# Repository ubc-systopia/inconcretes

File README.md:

<!-- # IVP System Guide -->

This repository contains source code and build documentation for a physical inverted pendulum test platform. The physical system, seen below, works to keep the pendulum shaft upright by actuating a pendulum cart along a track. To achieve this, we use a PID controller program that runs on a network of 4 Raspberry Pis. The Pis are able to communicate with each other using a distributed key value store. 

## Controls

### PID Control

PID Control is used to actuate system and balance the pendulum. There are 2 PID algorithms running at different sampling rates (30 Hz for Position PID and 200 Hz for Angle PID were lower bounds in our testing). 

The PID algorithm tracks the error of a system over time and applies the following computation to it:

$$
  u(t)=K_pe(t)+ K_i \int_{a}^{b} e(\tau) \,d\tau + K_d \frac{d}{dt} e(t)
$$
<!--  -->
<!--  -->

The proportional term of $K_pe(t)$ can be thought of as **reacting immediately to the current error**, the integralterm as **accumulating past errors over time**, and the derivative as **predicting future error trends**. PID control offers a cost-effective and straightforward solution compared to more complex control methods. 

The position PID algorithm takes the Cart Position as an input. This is given by an ultrasonic sensors on the sides of the assembly, then filtered before being passed as an input. The position PID algorithm then computes an output which we call an Angle Offset. This is an offset to the real angle of the pendulum and works to amplify the response of the angle controller when the cart nears the edges of the track. Without this controller, the pendulum has no incentive to remain with the bounds of the track.

The angle controller takes the current angle of the pendulum along with the offset provided by the position controller and computes the appropriate signal to send to the motor accordingly. A larger deviation from the desired angle results in more force applied by the motor to correct the pendulum.

## System Overview

### Starting with a Single Node Setup

A diagram for the system for a single node configuration is seen above.  

The physical build consists of the pendulum itself, with a Rotary Encoder, 2 Ultrasonic sensors, 2 limit switches and a motor driver. 

In order to control the pendulum we periodically drive the motor on the pendulum using a PWM signal, which is scaled and given direction based on the state of the system, using the PID scheme outlined above.

The single node in the setup is running 2 periodic tasks at different periods, a **Position Control Loop** and an **Angle Control Loop**. At the Position Control Loop we read a filtered position of the cart and use this as input to the Position PID algorithm. The output is saved to our Key Value Store and is shared with the Angle Control Loop through a shared memory location. 

The **Rotary Encoder BP** is a microcontroller running a continuous loop which reads the **Rotary Encoder** to find the current angle of the pendulum in every loop and forwards this value to the **Angle Control Loop**. The **Angle Control Loop** also receives a reading for the cart's current position along the track from **Ultrasonic 1**. 

 The **Angle Control Loop** performs some filtering of the position and shared this back to the Position Control Loop through a shared memory location. The **Angle Control Loop** uses the output of the position control loop for the angle PID algorithm to give us the output to the Pendulum. This output is in the form a scalar value that is then translated to the duty cycle and direction of a PWM signal.

The **Motor BP** is another microcontroller that is running a continuous loop where it receives the PWM signal from the **Angle Control Loop** and forwards it to the motor driver which then actuates the actual pendulum to achieve control. 

### Moving to a Multi Node Setup

<!--  -->

In a Multi Node Setup,, we have a maximum of 4 Raspberry Pi Nodes. Each of these is running an **Angle Control Loop** and a **Position Control Loop**. 2 Pis are capable of receiving position values from an independent Ultrasonic Sensor, and all 4 Pis are capable of receiving angular values from the **Rotary Encoder BP**. 

Position values can be shared across the Pis using the KVS, along with the control output from each Pi, along with any other values.

Each Pi computes its own control output, comprised of the PWM and Direction signals which are sent to the **Motor BP**. The **Motor BP** is then responsible for deciding on the output to send to the **Motor Driver**, which actuates the cart along the pendulum platform.

## Running on Raspberry Pis

We assume the following:
  - 4 raspberry pi nodes with hostnames `achal01-achal04`
  - nodes can access each other via SSH without passwords
  - this repository is cloned in the home directory of each node
  - PTP is installed
  
### PTP and VLAN config

Run `ifconfig`, expected output:

    eth0: flags=4163<UP,BROADCAST,RUNNING,MULTICAST>  mtu 1500
            inet 198.162.55.144  netmask 255.255.254.0  broadcast 198.162.55.255
            inet6 fe80::3a6:5deb:2c59:cd7f  prefixlen 64  scopeid 0x20<link>
            ether dc:a6:32:cd:ce:77  txqueuelen 1000  (Ethernet)
            RX packets 130046388  bytes 273546776 (260.8 MiB)
            RX errors 0  dropped 0  overruns 0  frame 0
            TX packets 131685298  bytes 406542628 (387.7 MiB)
            TX errors 0  dropped 0 overruns 0  carrier 0  collisions 0

    lo: flags=73<UP,LOOPBACK,RUNNING>  mtu 65536
            inet 127.0.0.1  netmask 255.0.0.0
            inet6 ::1  prefixlen 128  scopeid 0x10<host>
            loop  txqueuelen 1000  (Local Loopback)
            RX packets 76902811  bytes 8946060175 (8.3 GiB)
            RX errors 0  dropped 0  overruns 0  frame 0
            TX packets 76902811  bytes 8946060175 (8.3 GiB)
            TX errors 0  dropped 0 overruns 0  carrier 0  collisions 0

Run the following commands:
  ```bash
    sudo ip link add link eth0 name eth0.11 type vlan id 1 egress 0:2 1:2 2:2 3:2 4:2 5:2 6:2 7:2
    sudo ip link add link eth0 name eth0.12 type vlan id 2 egress 0:4 1:4 2:4 3:4 4:4 5:4 6:4 7:4
  ```
Again run `ifconfig`, expected output:
```
eth0: flags=4163<UP,BROADCAST,RUNNING,MULTICAST>  mtu 1500
        inet 198.162.55.144  netmask 255.255.254.0  broadcast 198.162.55.255
        inet6 fe80::3a6:5deb:2c59:cd7f  prefixlen 64  scopeid 0x20<link>
        ether dc:a6:32:cd:ce:77  txqueuelen 1000  (Ethernet)
        RX packets 130046461  bytes 273556620 (260.8 MiB)
        RX errors 0  dropped 0  overruns 0  frame 0
        TX packets 131685371  bytes 406551468 (387.7 MiB)
        TX errors 0  dropped 0 overruns 0  carrier 0  collisions 0

eth0.11: flags=4163<UP,BROADCAST,RUNNING,MULTICAST>  mtu 1500
        inet6 fe80::6584:daac:a387:87c4  prefixlen 64  scopeid 0x20<link>
        ether dc:a6:32:cd:ce:77  txqueuelen 1000  (Ethernet)
        RX packets 0  bytes 0 (0.0 B)
        RX errors 0  dropped 0  overruns 0  frame 0
        TX packets 4  bytes 686 (686.0 B)
        TX errors 0  dropped 0 overruns 0  carrier 0  collisions 0

eth0.12: flags=4163<UP,BROADCAST,RUNNING,MULTICAST>  mtu 1500
        inet6 fe80::824d:a435:2f9b:ca3a  prefixlen 64  scopeid 0x20<link>
        ether dc:a6:32:cd:ce:77  txqueuelen 1000  (Ethernet)
        RX packets 0  bytes 0 (0.0 B)
        RX errors 0  dropped 0  overruns 0  frame 0
        TX packets 7  bytes 976 (976.0 B)
        TX errors 0  dropped 0 overruns 0  carrier 0  collisions 0

lo: flags=73<UP,LOOPBACK,RUNNING>  mtu 65536
        inet 127.0.0.1  netmask 255.0.0.0
        inet6 ::1  prefixlen 128  scopeid 0x10<host>
        loop  txqueuelen 1000  (Local Loopback)
        RX packets 76902811  bytes 8946060175 (8.3 GiB)
        RX errors 0  dropped 0  overruns 0  frame 0
        TX packets 76902811  bytes 8946060175 (8.3 GiB)
        TX errors 0  dropped 0 overruns 0  carrier 0  collisions 0
```
Check the PTP status using systemctl status ptp4l and find the path of the ptp4l service

For example, the output will contain a line `Loaded: loaded ( ; enabled; vendor preset: enabled)`

Open file using  `sudo vim /lib/systemd/system/ptp4l.service` and check the ethernet interface used by PTP

By default, it is `eth0`, replace it with `eth0.11`

Run the following systemctl commands:
  ```bash
  sudo systemctl daemon-reload
  sudo systemctl restart ptp4l
  ```

### Running the Pendulum
<!-- 1. Run [`setup.sh`](http://setup.sh) on each Pi -->
1. Naviagate to this repository on Pi 1
2. Build the project:
    1. Navigate to the `build` directory
    2. run `cmake ..`
    3. run `make`
3. Enable UART on each of the Pis from the `raspi config` tool.
4. Callibrate pendulum by running the following command in the build directory of any of the connected Pis:
    ``` bash
    sudo ./test_AS5600
    ```
    This displays the rotary encoder angle, balance the pendulum manually and note the encoder value shown in the terminal. Ideally, this should be 2000 plus or minus 300, to keep the rollover state for angle outside the operating range of the pendulum.

5. Run the pendulum application from the project directory:

    ```bash
    sudo ./pivp_run.sh $NUM_NODES $POSITION_LOOP_PERIOD $ANGLE_LOOP_PERIOD $POSITION_KP $POSITION_KD $POSITION_KI $ANGLE_KP $ANGLE_KD $ANGLE_KI $POSITION_SET_POINT $ANGLE_SET_POINT
    ```

      Values that worked well for our system for the other parameters:

      | Parameter | Value |
      |--- | --- |
      |`NUM_NODES`| number of nodes you are running with| 
      | `POSITION_LOOP_PERIOD`: | 20 |
      | `ANGLE_LOOP_PERIOD`: | 6 |
      | `POSITION_KP`: | 0.01 |
      | `POSITION_KD`: | 0.08 |
      | `POSITION_KI`: | 0 |
      | `ANGLE_KP`: | 25 |
      | `ANGLE_KD`: | 2.5 |
      | `ANGLE_KI`: | 150 |
      | `POSITION_SET_POINT`: | 20 - Corresponds to distance from side to middle of track in cm |
      | `ANGLE_SET_POINT`: | calibration value from previous step |

6. Press either limit switch on sides of pendulum track to stop a run of the pendulum
7. Logs for the run are available at local nodes at ‘PiCtlLogs/date-of-runcompletion_time-of-completion_PiN’

## Pendulum Build Documentation
Detailled descriptions of how to build the pendulum and various aspects of the systemn are included in subdirectories of this project.
- [`Bluepill_Firmware`](Bluepill_Firmware): Firmware for 2 Bluepill microcontrollers used, along with instructions for how to flash the firmware on the devices.
- [`PCB_Designs_Docs`](PCB_Designs_Docs): All PCB design files for the custom PCBs used in the pendulum, including labelled circuit diagrams for reference, gerber and drill files for fabrication. Additionally, all electrical components and quantities, with purchase links are shown. 
- [`Mech_Docs`](Mech_Docs): All mechanical components with purchase links and quantities are included. Additionally, CAD design files, STL files for 3D printed parts and DXFs for laser cut parts are included.

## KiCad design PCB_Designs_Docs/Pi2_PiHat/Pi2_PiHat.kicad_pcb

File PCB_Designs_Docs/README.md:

# Inverted Pendulum Electrical Documentation and PCB Designs

## Components/Sensors Used

| Component | Quantity | Purchase Link | Notes |
| --- | --- | --- | --- |
| Ultrasonic Sensor | 2 | https://www.digikey.ca/short/wqjn48db |  |
| AS5600 Rotary Encoder | 1 | https://a.co/d/2jkT8j0 | Prebuilt breakout board with magnet included used |
| Brushed DC Motor | 1 | https://a.co/d/41Gn3cl | Any smooth motion motor with low cogging and similar specifications is usable. |
| Raspberry Pi 4B | 4 | -  | - |
| Bluepill (STM32F103C dev board) | 2 | https://a.co/d/aVWNCsf |  |
| ST-Link V2 | 1 | https://a.co/d/aVWNCsf |  |
| 12 V Motor Driver | 1 | https://www.cytron.io/p-10amp-5v-30v-dc-motor-driver |  |
| 12 V Power Supply | 1 | https://www.digikey.ca/short/t58bfrvt |  |
|  4.7 kOhm Resistor | 2 | https://www.digikey.ca/short/v238crf2 | For I2C Lines |
| JST Connector Set | 1 | https://a.co/d/0fB4Xf2 |  |
| I2C OLED Display Module | 2 | https://a.co/d/eMWrLmH |  |
| Header Pins (Male) | 8 | https://www.digikey.ca/short/54wwz4hv |  |
| Header Pins (Female) | 4 | https://www.digikey.ca/short/5cdf2dd4 |  |
| Custom PCBs | 4 | Download design files and manufacture at any PCB fab. | Details included below in PCB Design Section |
| PJ002A Connector | 1 | https://www.digikey.ca/short/v80h319m |  |
| AC DC Wall Power Adapter, Barrel Jack | 1 | https://www.digikey.ca/short/rw25c3v4 |  |
| Limit Switch | 2 | https://www.digikey.ca/short/8dmrj95d |  |

## PCB Design

In testing and integration of the system, I found that wiring using Dupont (jumper) wires to connect to the Pi headers was not a suitable long term solution as sensors would come unplugged and connections were unreliable. 

I elected to instead design a few custom Pi Hat PCBs that could plug into the Raspberry Pi 4Bs GPIO Headers. These PCBs included JST connectors for more permanent connections to sensors and allowed for cleaner, reliable wiring. To keep connections clean, zip ties and cable tie mounts were used to bundle and route wires.

Below are descriptions for the KiCad projects used to manufacture the PCBs for the project, as well as labelled diagrams of the PCB for an end user.

### **PCB Files**

Pi Hat (`Pi1_PiHat`):

This is the Pi Hat for the “main” Raspberry Pi. In a single node setup, this PCB alone with 1 Raspberry PI is sufficient. 

<!--  -->

| Number | Label | Description |
| --- | --- | --- |
| 1 | AS5600 Distributor Bluepill | BP responsible for receiving AS5600 communication over I2C and sending this over UART to all connected Pis |
| 2 | PWM Forwarder Bluepill | BP responsible for receiving the PWM signal from all Pi’s and sending the final output PWM signal to the motor |
| 3 | Board to Pi Header | Connects to 40 pin Pi Header |
| 4 | Pi Header Extension | Allows access to all Pi Header pins |
| 5 | I2C Pullup Resistors |  |
| 6 | Barrel Jack (PJ002A) | 3V3 Power Input for Bluepills |
| 7 | Limit Switch 1 Connector | Limit switch input, allows detection for when cart is at rails of the physical track |
| 8 | AS5600 Connector 1 | Connector for I2C comms, direction signal and programming pins of AS5600 |
| 9 | AS5600 Connector 2 | Connector for power, ground and analog output of AS5600 |
| 10 | BP to Motor Connector | Connection to share ground, send direction and PWM to the motor driver |
| 11 | Limit Switch 2 Connector | Limit switch input, allows detection for when cart is at rails of the physical track |
| 12 | Ultrasonic 1 Connector |  |
| 13 | Pi1 to Pi3 Connector | Connects ground, AS5600 Distributor BP UART Tx line, limit switches and motor instruction lines |
| 14 | Pi1 to Pi2 Connector | Connects ground, AS5600 Distributor BP UART Tx line, limit switches and motor instruction lines |
| 15 | Pi1 to Pi4 Connector | Connects ground, AS5600 Distributor BP UART Tx line, limit switches and motor instruction lines |
| 16 | PWM Forwarder BP to Display Connector | Connector for BP to digital display |
| 17 | AS5600 Distributor BP to Display Connector | Connector for BP to digital display |

Pi Hat 2 (`Pi2_PiHat`):

This is the Pi Hat for the secondary node for a simple two node setup. The second node has a connector to the “main” Pi Hat as well as an additional Ultrasonic sensor.

| Number | Label | Description |
| --- | --- | --- |
| 1 | Board to Pi Header | Connects to 40 pin Pi Header |
| 2 | Pi Header Extension | Allows access to all Pi Header pins |
| 3 | Ultrasonic 2 Connector |  |
| 4 | Pi1 to Pi2 Connector | Connects ground, AS5600 Distributor BP UART Tx line, limit switches and motor instruction lines |

Pi Hat N (`PiN_PiHat`):

| Number | Label | Description |
| --- | --- | --- |
| 1 | Board to Pi Header | Connects to 40 pin Pi Header |
| 2 | Pi Header Extension | Allows access to all Pi Header pins |
| 4 | Pi1 to PiN Connector | Connects ground, AS5600 Distributor BP UART Tx line, limit switches and motor instruction lines |

This is the Pi Hat for all additional nodes. It includes a connector to the main Pi Hat to share ground, a UART line, limit switch input, and outputs to the motor driving Bluepill.

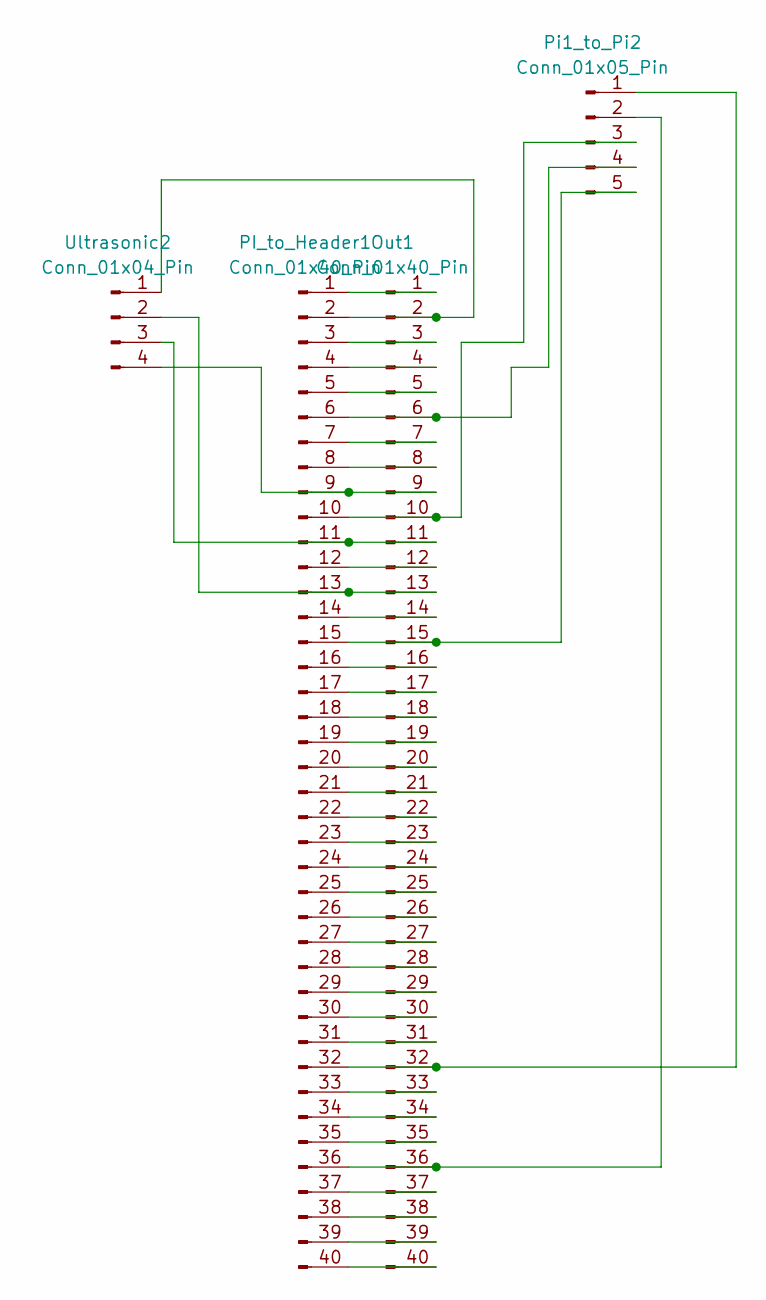
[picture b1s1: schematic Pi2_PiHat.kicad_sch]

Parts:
Out1: Conn_01x40_Pin; TE_7-146256-0
PI_to_Header1: Conn_01x40_Pin; TE_7-146256-0
Pi1_to_Pi2: Conn_01x05_Pin; JST_EH_B5B-EH-A_1x05_P2.50mm_Vertical
Ultrasonic2: Conn_01x04_Pin; JST_EH_B4B-EH-A_1x04_P2.50mm_Vertical

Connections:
unnamed: Out1.1, PI_to_Header1.1
unnamed: Out1.2, PI_to_Header1.2, Ultrasonic2.1
unnamed: Out1.3, PI_to_Header1.3
unnamed: Out1.4, PI_to_Header1.4
unnamed: Out1.5, PI_to_Header1.5
unnamed: Out1.6, PI_to_Header1.6, Pi1_to_Pi2.4
unnamed: Out1.7, PI_to_Header1.7
unnamed: Out1.8, PI_to_Header1.8
unnamed: Out1.9, PI_to_Header1.9, Ultrasonic2.4
unnamed: Out1.10, PI_to_Header1.10, Pi1_to_Pi2.3
unnamed: Out1.11, PI_to_Header1.11, Ultrasonic2.3
unnamed: Out1.12, PI_to_Header1.12
unnamed: Out1.13, PI_to_Header1.13, Ultrasonic2.2
unnamed: Out1.14, PI_to_Header1.14
unnamed: Out1.15, PI_to_Header1.15, Pi1_to_Pi2.5
unnamed: Out1.16, PI_to_Header1.16
unnamed: Out1.17, PI_to_Header1.17
unnamed: Out1.18, PI_to_Header1.18
unnamed: Out1.19, PI_to_Header1.19
unnamed: Out1.20, PI_to_Header1.20
unnamed: Out1.21, PI_to_Header1.21
unnamed: Out1.22, PI_to_Header1.22
unnamed: Out1.23, PI_to_Header1.23
unnamed: Out1.24, PI_to_Header1.24
unnamed: Out1.25, PI_to_Header1.25
unnamed: Out1.26, PI_to_Header1.26
unnamed: Out1.27, PI_to_Header1.27
unnamed: Out1.28, PI_to_Header1.28
unnamed: Out1.29, PI_to_Header1.29
unnamed: Out1.30, PI_to_Header1.30
unnamed: Out1.31, PI_to_Header1.31
unnamed: Out1.32, PI_to_Header1.32, Pi1_to_Pi2.1
unnamed: Out1.33, PI_to_Header1.33
unnamed: Out1.34, PI_to_Header1.34
unnamed: Out1.35, PI_to_Header1.35
unnamed: Out1.36, PI_to_Header1.36, Pi1_to_Pi2.2
unnamed: Out1.37, PI_to_Header1.37
unnamed: Out1.38, PI_to_Header1.38
unnamed: Out1.39, PI_to_Header1.39
unnamed: Out1.40, PI_to_Header1.40

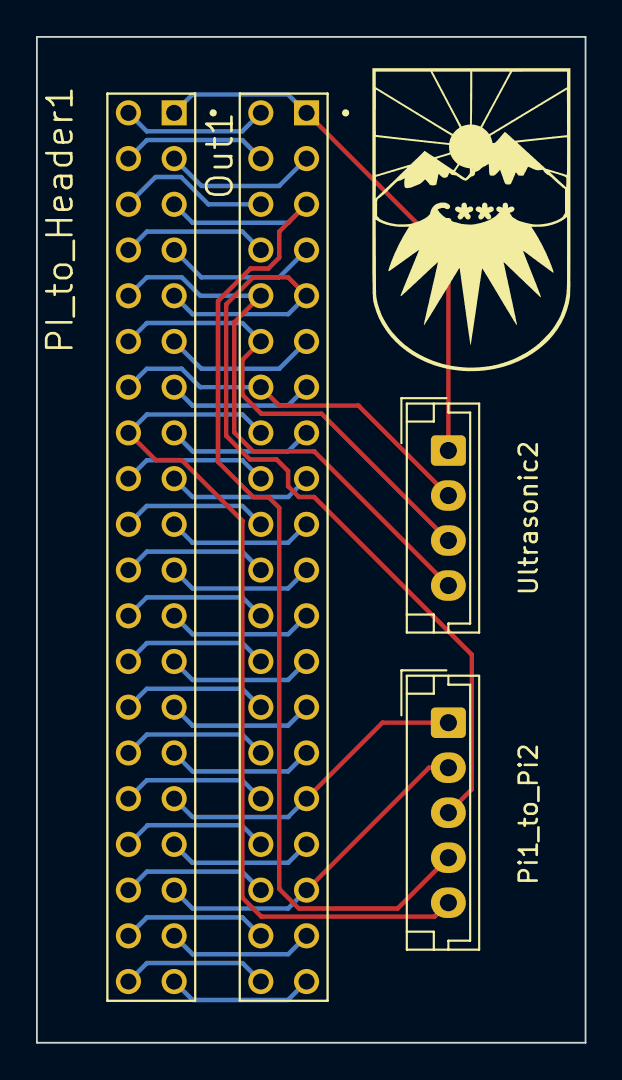
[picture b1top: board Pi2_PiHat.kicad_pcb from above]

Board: 2 copper layers, 30.5 x 55.9 mm, 4 parts (0 on the bottom side), 40 nets.

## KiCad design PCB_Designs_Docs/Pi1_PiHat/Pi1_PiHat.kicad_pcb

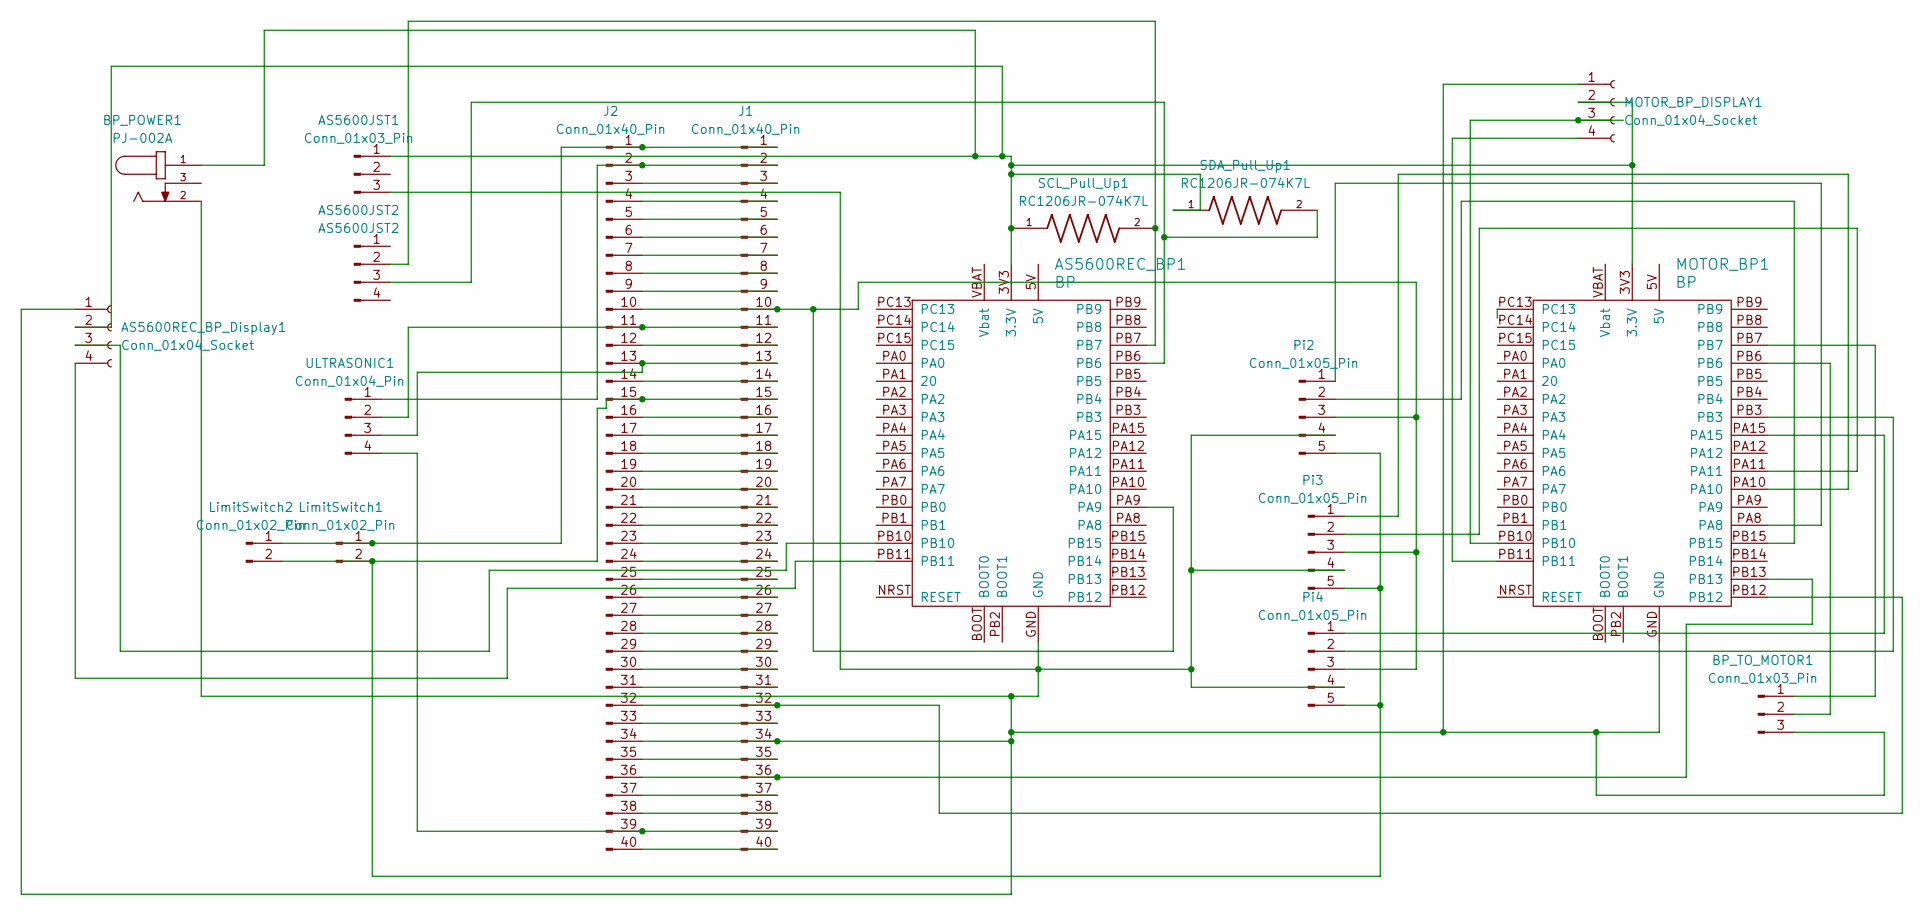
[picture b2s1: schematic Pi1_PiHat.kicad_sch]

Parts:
AS5600JST1: Conn_01x03_Pin; JST_EH_B3B-EH-A_1x03_P2.50mm_Vertical
AS5600JST2: AS5600JST2; JST_EH_B4B-EH-A_1x04_P2.50mm_Vertical
AS5600REC_BP1: BP; DevBoard_STM32_Bluepill
AS5600REC_BP_Display1: Conn_01x04_Socket; PinSocket_1x04_P2.54mm_Vertical
BP_POWER1: PJ-002A; CUI_PJ-002A; DigiKey_Part_Number CP-002A-ND
BP_TO_MOTOR1: Conn_01x03_Pin; JST_EH_B3B-EH-A_1x03_P2.50mm_Vertical
J1, J2: Conn_01x40_Pin; TE_7-146256-0
LimitSwitch1, LimitSwitch2: Conn_01x02_Pin; JST_EH_B2B-EH-A_1x02_P2.50mm_Vertical
MOTOR_BP1: BP; DevBoard_STM32_Bluepill
MOTOR_BP_DISPLAY1: Conn_01x04_Socket; PinSocket_1x04_P2.54mm_Vertical
Pi2, Pi3, Pi4: Conn_01x05_Pin; JST_EH_B5B-EH-A_1x05_P2.50mm_Vertical
SCL_Pull_Up1: RC1206JR-074K7L; RESC3116X65N; DigiKey_Part_Number 311-4.7KERTR-ND
SDA_Pull_Up1: RC1206JR-074K7L; RESC3116X65N; DigiKey_Part_Number 311-4.7KERTR-ND
ULTRASONIC1: Conn_01x04_Pin; JST_EH_B4B-EH-A_1x04_P2.50mm_Vertical

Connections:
unnamed: AS5600JST1.1, AS5600REC_BP1.3V3 (3.3V), AS5600REC_BP_Display1.2, BP_POWER1.1, MOTOR_BP1.3V3 (3.3V), MOTOR_BP_DISPLAY1.2, SCL_Pull_Up1.1, SDA_Pull_Up1.1
unnamed: AS5600JST1.3, AS5600REC_BP1.GND, AS5600REC_BP_Display1.1, BP_POWER1.2, BP_TO_MOTOR1.3, J1.34, J2.34, MOTOR_BP1.GND, MOTOR_BP_DISPLAY1.1, Pi2.4, Pi3.4, Pi4.4
unnamed: AS5600JST2.2, AS5600REC_BP1.PB7, SCL_Pull_Up1.2
unnamed: AS5600JST2.3, AS5600REC_BP1.PB6, SDA_Pull_Up1.2
unnamed: AS5600REC_BP1.PB10, AS5600REC_BP_Display1.3
unnamed: AS5600REC_BP1.PB11, AS5600REC_BP_Display1.4
unnamed: BP_TO_MOTOR1.1, MOTOR_BP1.PB7
unnamed: BP_TO_MOTOR1.2, MOTOR_BP1.PB6
unnamed: J1.1, J2.1, LimitSwitch1.1, LimitSwitch2.1
unnamed: J1.2, J2.2, ULTRASONIC1.1
unnamed: J1.3, J2.3
unnamed: J1.4, J2.4
unnamed: J1.5, J2.5
unnamed: J1.6, J2.6
unnamed: J1.7, J2.7
unnamed: J1.8, J2.8
unnamed: J1.9, J2.9
unnamed: AS5600REC_BP1.PA9, J1.10, J2.10, Pi2.3, Pi3.3, Pi4.3
unnamed: J1.11, J2.11, ULTRASONIC1.2
unnamed: J1.12, J2.12
unnamed: J1.13, J2.13, ULTRASONIC1.3
unnamed: J1.14, J2.14
unnamed: J1.15, J2.15, LimitSwitch1.2, LimitSwitch2.2, Pi2.5, Pi3.5, Pi4.5
unnamed: J1.16, J2.16
unnamed: J1.17, J2.17
unnamed: J1.18, J2.18
unnamed: J1.19, J2.19
unnamed: J1.20, J2.20
unnamed: J1.21, J2.21
unnamed: J1.22, J2.22
unnamed: J1.23, J2.23
unnamed: J1.24, J2.24
unnamed: J1.25, J2.25
unnamed: J1.26, J2.26
unnamed: J1.27, J2.27
unnamed: J1.28, J2.28
unnamed: J1.29, J2.29
unnamed: J1.30, J2.30
unnamed: J1.31, J2.31
unnamed: J1.32, J2.32, MOTOR_BP1.PB12
unnamed: J1.33, J2.33
unnamed: J1.35, J2.35
unnamed: J1.36, J2.36, MOTOR_BP1.PB13
unnamed: J1.37, J2.37
unnamed: J1.38, J2.38
unnamed: J1.39, J2.39, ULTRASONIC1.4
unnamed: J1.40, J2.40
unnamed: MOTOR_BP1.PB10, MOTOR_BP_DISPLAY1.3
unnamed: MOTOR_BP1.PB11, MOTOR_BP_DISPLAY1.4
unnamed: MOTOR_BP1.PA8, Pi2.1
unnamed: MOTOR_BP1.PB15, Pi2.2
unnamed: MOTOR_BP1.PA10, Pi3.1
unnamed: MOTOR_BP1.PA11, Pi3.2
unnamed: MOTOR_BP1.PA15, Pi4.1
unnamed: MOTOR_BP1.PB3, Pi4.2

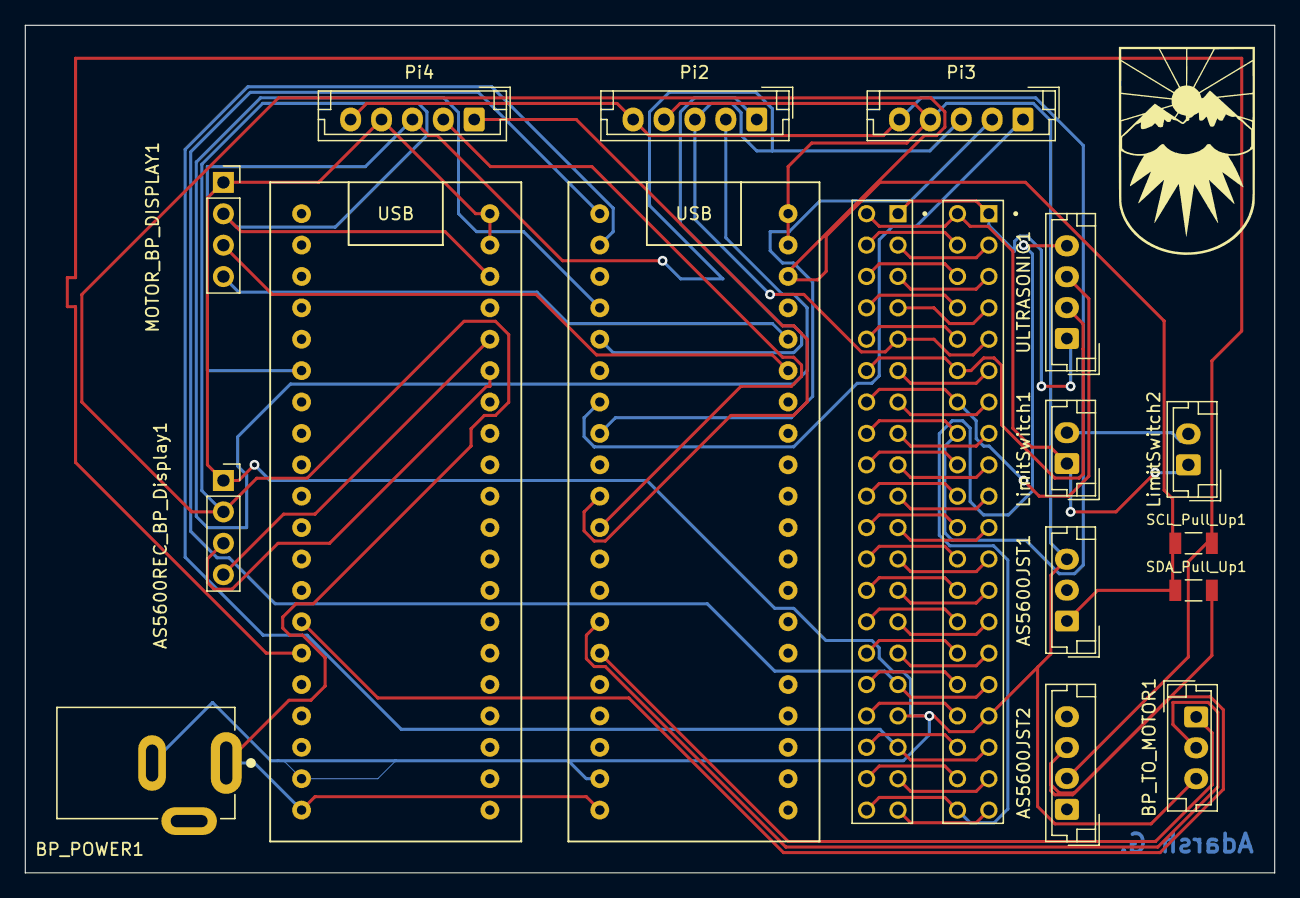
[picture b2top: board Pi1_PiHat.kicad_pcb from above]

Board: 2 copper layers, 101.1 x 68.6 mm, 18 parts (0 on the bottom side), 55 nets.

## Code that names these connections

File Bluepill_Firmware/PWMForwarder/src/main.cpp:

#include <Wire.h>
#include <Adafruit_SSD1306.h>
#include <vector>

#define SCREEN_WIDTH 128 // OLED display width, in pixels
#define SCREEN_HEIGHT 64 // OLED display height, in pixels
#define OLED_RESET 	-1 // This display does not have a reset pin accessible

#define PI1_PWM PB12
#define PI2_PWM PA8
#define PI3_PWM PA10
#define PI4_PWM PB3

#define PI1_DIR PB13
#define PI2_DIR PB15
#define PI3_DIR PA11
#define PI4_DIR PA15
    
#define PWM_OUT PB_6
#define DIR_OUT PB7

TwoWire Wire2(PB11, PB10);
Adafruit_SSD1306 display_handler(SCREEN_WIDTH, SCREEN_HEIGHT, &Wire2, OLED_RESET);
// Serial object to transmit to raspberry pis
int iterCount=0;
int pwmOutFreq=50000;
double piInputPeriod=5.0;
bool emptyVec=0;
long pulseTime1=0;
long pulseTime2=0;
long pulseTime3=0;
long pulseTime4=0;
int dir1=0;
int dir2=0;
int dir3=0;
int dir4=0;
long medianPulseTime=0;
long outputDutyCycle=0;
int dir=0;


void setup_display(Adafruit_SSD1306 &display_handler){
    display_handler.begin(SSD1306_SWITCHCAPVCC, 0x3C);
    // Displays Adafruit logo by default. call clearDisplay immediately if you don't want this.
    display_handler.display();
    delay(2000);

    // Displays "Hello world!" on the screen
    display_handler.clearDisplay();
    display_handler.setTextSize(1);
    display_handler.setTextColor(SSD1306_WHITE);
    display_handler.setCursor(0,0);
    display_handler.println("Hello world!");
    display_handler.display();
}

void initialize_pins(){
    pinMode(PI1_PWM, INPUT);
    pinMode(PI2_PWM, INPUT);
    pinMode(PI3_PWM, INPUT);
    pinMode(PI4_PWM, INPUT);

    pinMode(PI1_DIR, INPUT);
    pinMode(PI2_DIR, INPUT);
    pinMode(PI3_DIR, INPUT);
    pinMode(PI4_DIR, INPUT);

    pinMode(PWM_OUT, OUTPUT);
    pinMode(DIR_OUT, OUTPUT);
    pwm_start(PWM_OUT, pwmOutFreq, 0, TimerCompareFormat_t::RESOLUTION_12B_COMPARE_FORMAT);
}

void read_pi_inputs(){
    pulseTime1=pulseIn(PI1_PWM, HIGH, 1000);//(pow(10,7));
    pulseTime2=pulseIn(PI2_PWM, HIGH, 1000);//(pow(10,7));
    pulseTime3=pulseIn(PI3_PWM, HIGH, 1000);//(pow(10,7));
    pulseTime4=pulseIn(PI4_PWM, HIGH, 1000);//(pow(10,7));

    dir1=digitalRead(PI1_DIR);
    dir2=digitalRead(PI2_DIR);
    dir3=digitalRead(PI3_DIR);
    dir4=digitalRead(PI4_DIR);
}

void compute_median(){
    // create vector of pulse times if pulse time is not 0
    std::vector<long> pulseTimes;
    // if dir1 is high, give pulseTime1 a negative sign 
    if(pulseTime1) {if(dir1) pulseTime1=-pulseTime1; pulseTimes.push_back(pulseTime1);};
    if(pulseTime2) {if(dir2) pulseTime2=-pulseTime2; pulseTimes.push_back(pulseTime2);};
    if(pulseTime3) {if(dir3) pulseTime3=-pulseTime3; pulseTimes.push_back(pulseTime3);};
    if(pulseTime4) {if(dir4) pulseTime4=-pulseTime4; pulseTimes.push_back(pulseTime4);};
    

    // find median of pulse times
    if(!pulseTimes.size()){
        display_handler.clearDisplay();
        display_handler.setCursor(0,0);
        emptyVec=!emptyVec;
        display_handler.println("Empty Vector: " + String(emptyVec));
        display_handler.display();
    } else{
        std::sort(pulseTimes.begin(), pulseTimes.end());
        long range=abs(pulseTimes[pulseTimes.size()-1]-pulseTimes[0]);
        std::sort(pulseTimes.begin(), pulseTimes.end());
        medianPulseTime=double(pulseTimes[pulseTimes.size()/2]);
        outputDutyCycle=abs(double(medianPulseTime))/piInputPeriod;
        dir=medianPulseTime<0;
        display_handler.clearDisplay();
        display_handler.setCursor(0,0);
        display_handler.println("size: " + String(pulseTimes.size()));
        display_handler.println("Med D.C: " + String(abs(double(outputDutyCycle))));
        display_handler.println("pulseTimes[0] :" + String(double(pulseTimes[0])));
        display_handler.println("Med: " + String(double(medianPulseTime)));
        display_handler.println("Pi1 P.T: " + String(pulseTime1));
        display_handler.println("Pi1 Dut: " + String(double(pulseTime1)/piInputPeriod));
        display_handler.println("Range: " + String(range));
        display_handler.println("Direction: " + String(dir));
        display_handler.display();
    }
}

void output_to_motor_driver(){
    pwm_start(PWM_OUT, pwmOutFreq, outputDutyCycle, TimerCompareFormat_t::PERCENT_COMPARE_FORMAT);
    digitalWrite(DIR_OUT, dir);
}

// ARDUINO SETUP LOOP
void setup() {
    setup_display(display_handler);
    initialize_pins();
}


// ARDUINO MAIN LOOP
void loop() {
    unsigned long outputDutyCycle=0;
    int dir=0;

    read_pi_inputs();

    compute_median();
    // outputs previously computed median to the motor driver
    output_to_motor_driver();
    // display_handler.clearDisplay();
    // display_handler.setCursor(0,0);
    // display_handler.println("Itercount: " + String(iterCount++));
    // // // display_handler.println("Pulse time: " + String(pulseTime));
    // display_handler.println("Duty cycle: " + String(outputDutyCycle));
    // display_handler.println("Direction: " + String(dir));
    // // // display_handler.println("Pi number: " + String(piNum));
    // display_handler.display();
    // display_handler.clearDisplay();
};

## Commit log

2022-11-28 Porting Achal from our private repo
2024-01-17 initial public commit
